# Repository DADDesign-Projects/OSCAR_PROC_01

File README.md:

# OSCAR Processor Board - OSCAR_PROC_01

# 📋 Description
Dedicated electronic board implementing the processor section of the OSCAR effects pedal (https://github.com/DADDesign-Projects/OSCAR_P01A01). This board handles digital signal processing and audio control for the OSCAR effects platform.

# 🛠️ Technical Specifications
## Microcontroller STM32H743:
 - High-performance ARM Cortex-M7 MCU
 -  480 MHz frequency
 -  2MB Flash memory
 -  1MB RAM
## Flash Memory 2* W25Q128
 - 32 Moctet.
 - Double mode 8 bits SPI;
 - 120 Mhz
## SDRAM Memory IS42S16320
 - 64 Moctet
 - 200 Mhz
## USB OTG FS
  - CDC Virtual port COM
  - UDP DownLoad Firmware Update
  - MIDI / USB
## I/O
  - 4 Encoders
  - 2 Switchs
## TFT
  - SPI inteface 
  - 2.4 inch 
## MIDI
  - UART TRS Midi in
## Orogramming/Debugging
  - STLink serial port
  - USB UDP protocol.

## 💻 Software
The circuit design software for this board is available in the OSCAR repository (https://github.com/DADDesign-Projects/OSCAR_P01A01). This project is built upon the DAD Forge framework (https://github.com/DADDesign-Projects/DAD_FORGE), which provides a standardized foundation for hardware development and collaboration.

## 🛠️ Design Tools
This project was entirely designed using KiCad 9.0, the open-source electronics design automation suite.
    
# 📬 Contact
Feel free to contact me for any questions, feedback, improvement suggestions, or collaboration proposals related to the FORGE framework or the OSCAR hardware platform.
I am always open to discussion and community contributions (daddesign.projects@gmail.com).  
  
---

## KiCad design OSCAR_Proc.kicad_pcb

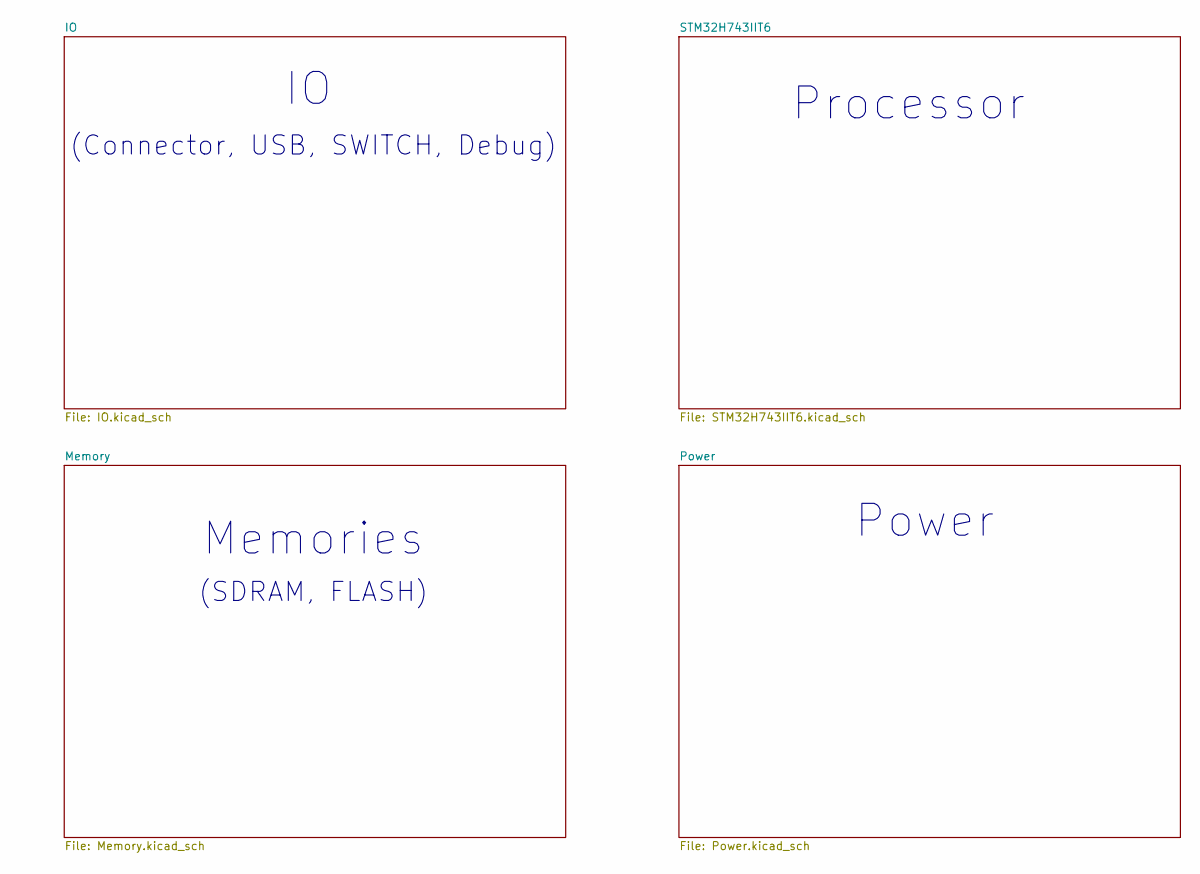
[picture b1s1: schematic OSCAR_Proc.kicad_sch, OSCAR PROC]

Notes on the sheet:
Processor
(Connector, USB, SWITCH, Debug)
Power
(SDRAM, FLASH)
Memories

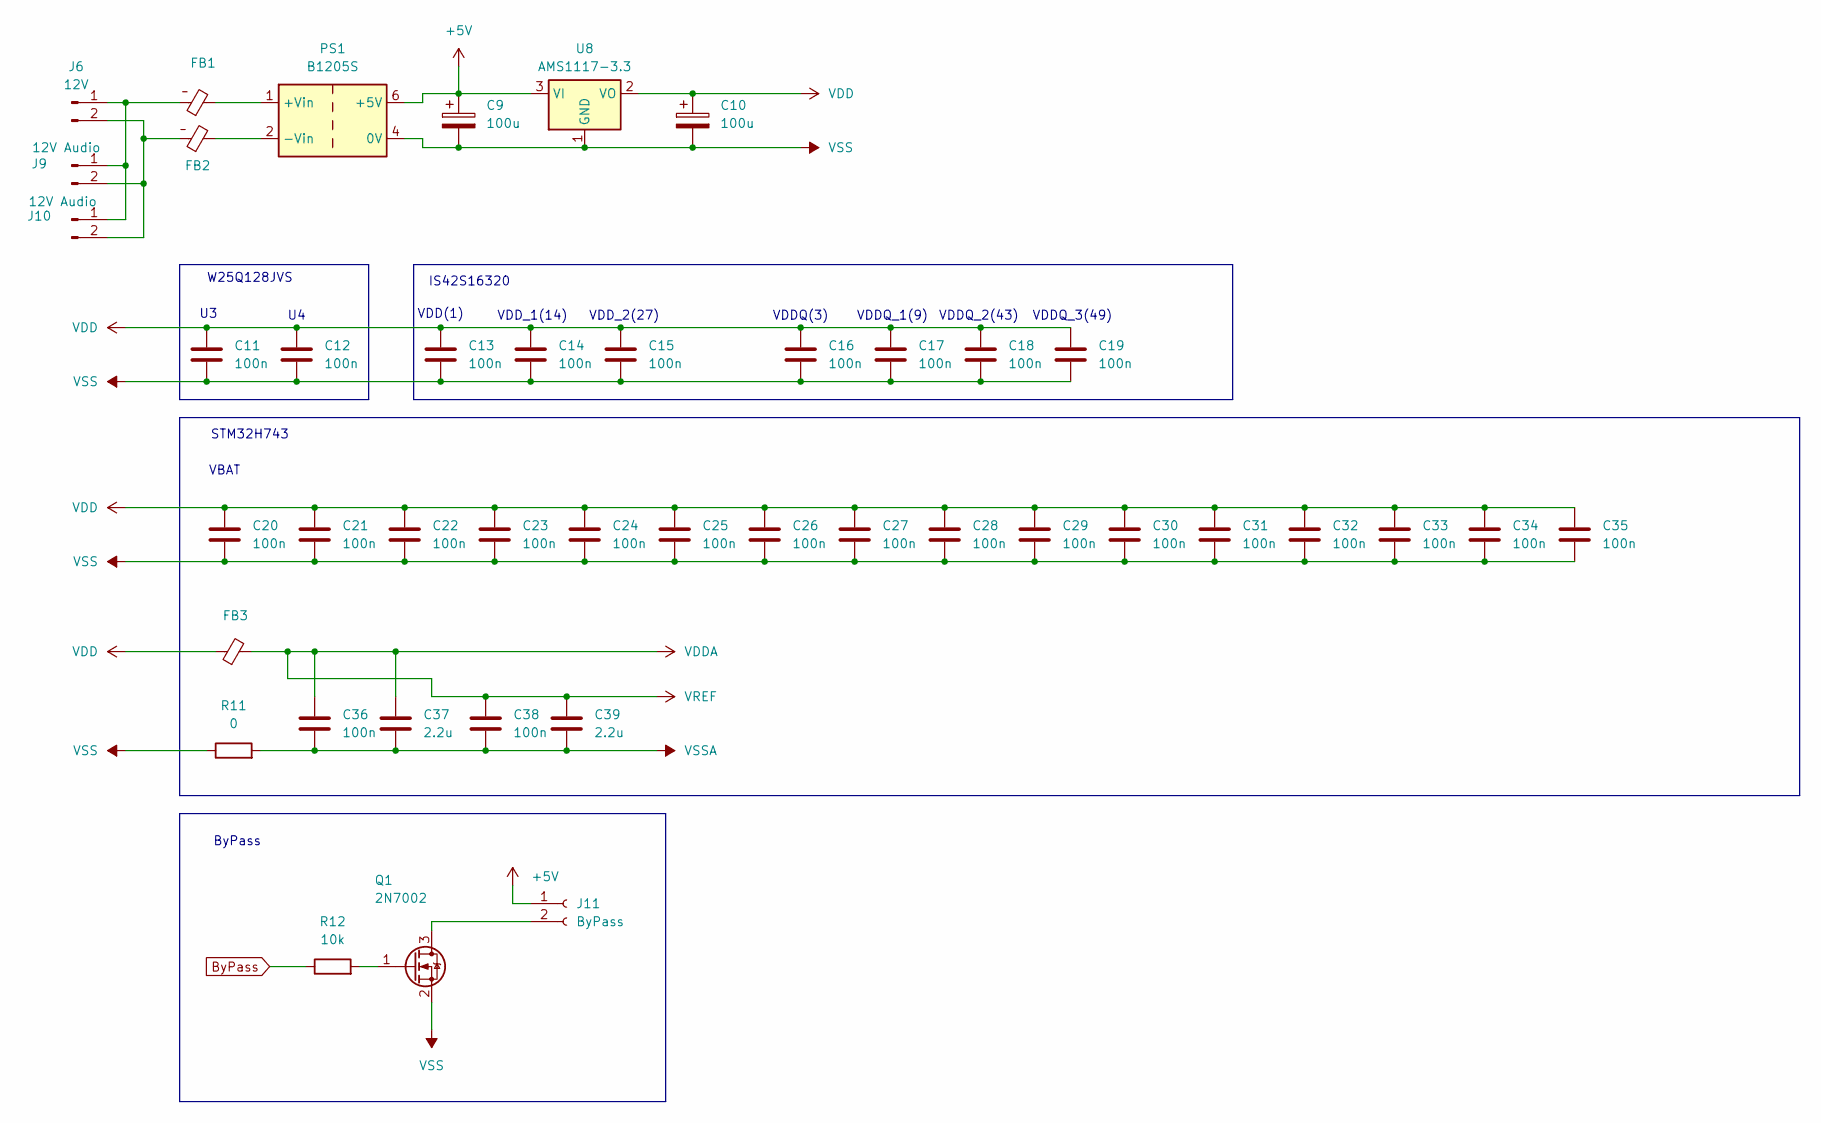
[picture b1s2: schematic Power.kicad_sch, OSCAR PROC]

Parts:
C9, C10: 100u; CP_Elec_6.3x9.9_WM
C11, C12, C13, C14, C15, C16, C17, C18, C19, C20, C21, C22, C23, C24, C25, C26, C27, C28, C29, C30, C31, C32, C33, C34, C35, C36, C38: 100n; C_0805_2012Metric_Pad1.18x1.45mm_HandSolder
C37, C39: 2.2u; C_0805_2012Metric_Pad1.18x1.45mm_HandSolder
FB1, FB2: L_1206_3216Metric_Pad1.22x1.90mm_HandSolder
FB3: L_0805_2012Metric_Pad1.15x1.40mm_HandSolder
J6: 12V; PinHeader_1x02_P2.54mm_Vertical
J9, J10: 12V Audio; PinSocket_1x02_P2.54mm_Vertical
J11: ByPass; PinSocket_1x02_P2.54mm_Vertical
PS1: B1205S; Converter_DCDC_TRACO_TBA1-xxxxE_Single_THT
Q1: 2N7002; SOT-23
R11: 0; R_1206_3216Metric_Pad1.30x1.75mm_HandSolder
R12: 10k; R_1206_3216Metric_Pad1.30x1.75mm_HandSolder
U8: AMS1117-3.3; SOT-223-3_TabPin2

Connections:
+5V: C9.1, J11.1, PS1.6 (+5V), U8.3 (VI)
ByPass: R12.1; also elsewhere on the board
unnamed: FB1.1, J6.1, J9.1, J10.1
unnamed: FB2.1, J6.2, J9.2, J10.2
unnamed: J11.2, Q1.3 (D)
unnamed: FB1.2, PS1.1 (+Vin)
unnamed: FB2.2, PS1.2 (-Vin)
unnamed: Q1.1 (G), R12.2
VDD: C10.1, C11.1, C12.1, C13.1, C14.1, C15.1, C16.1, C17.1, C18.1, C19.1, C20.1, C21.1, C22.1, C23.1, C24.1, C25.1, C26.1, C27.1, C28.1, C29.1, C30.1, C31.1, C32.1, C33.1, C34.1, C35.1, FB3.1, U8.2 (VO); also elsewhere on the board
VDDA: C36.1, C37.1, C38.1, C39.1, FB3.2; also elsewhere on the board
VSS: C9.2, C10.2, C11.2, C12.2, C13.2, C14.2, C15.2, C16.2, C17.2, C18.2, C19.2, C20.2, C21.2, C22.2, C23.2, C24.2, C25.2, C26.2, C27.2, C28.2, C29.2, C30.2, C31.2, C32.2, C33.2, C34.2, C35.2, PS1.4 (0V), Q1.2 (S), R11.1, U8.1 (GND); also elsewhere on the board
VSSA: C36.2, C37.2, C38.2, C39.2, R11.2; also elsewhere on the board

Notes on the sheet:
VDDQ_3(49)
ByPass
STM32H743
VDD(1)
VDD_1(14)
VDD_2(27)
VBAT
IS42S16320
VDDQ(3)
W25Q128JVS
VDDQ_1(9)
VDDQ_2(43)

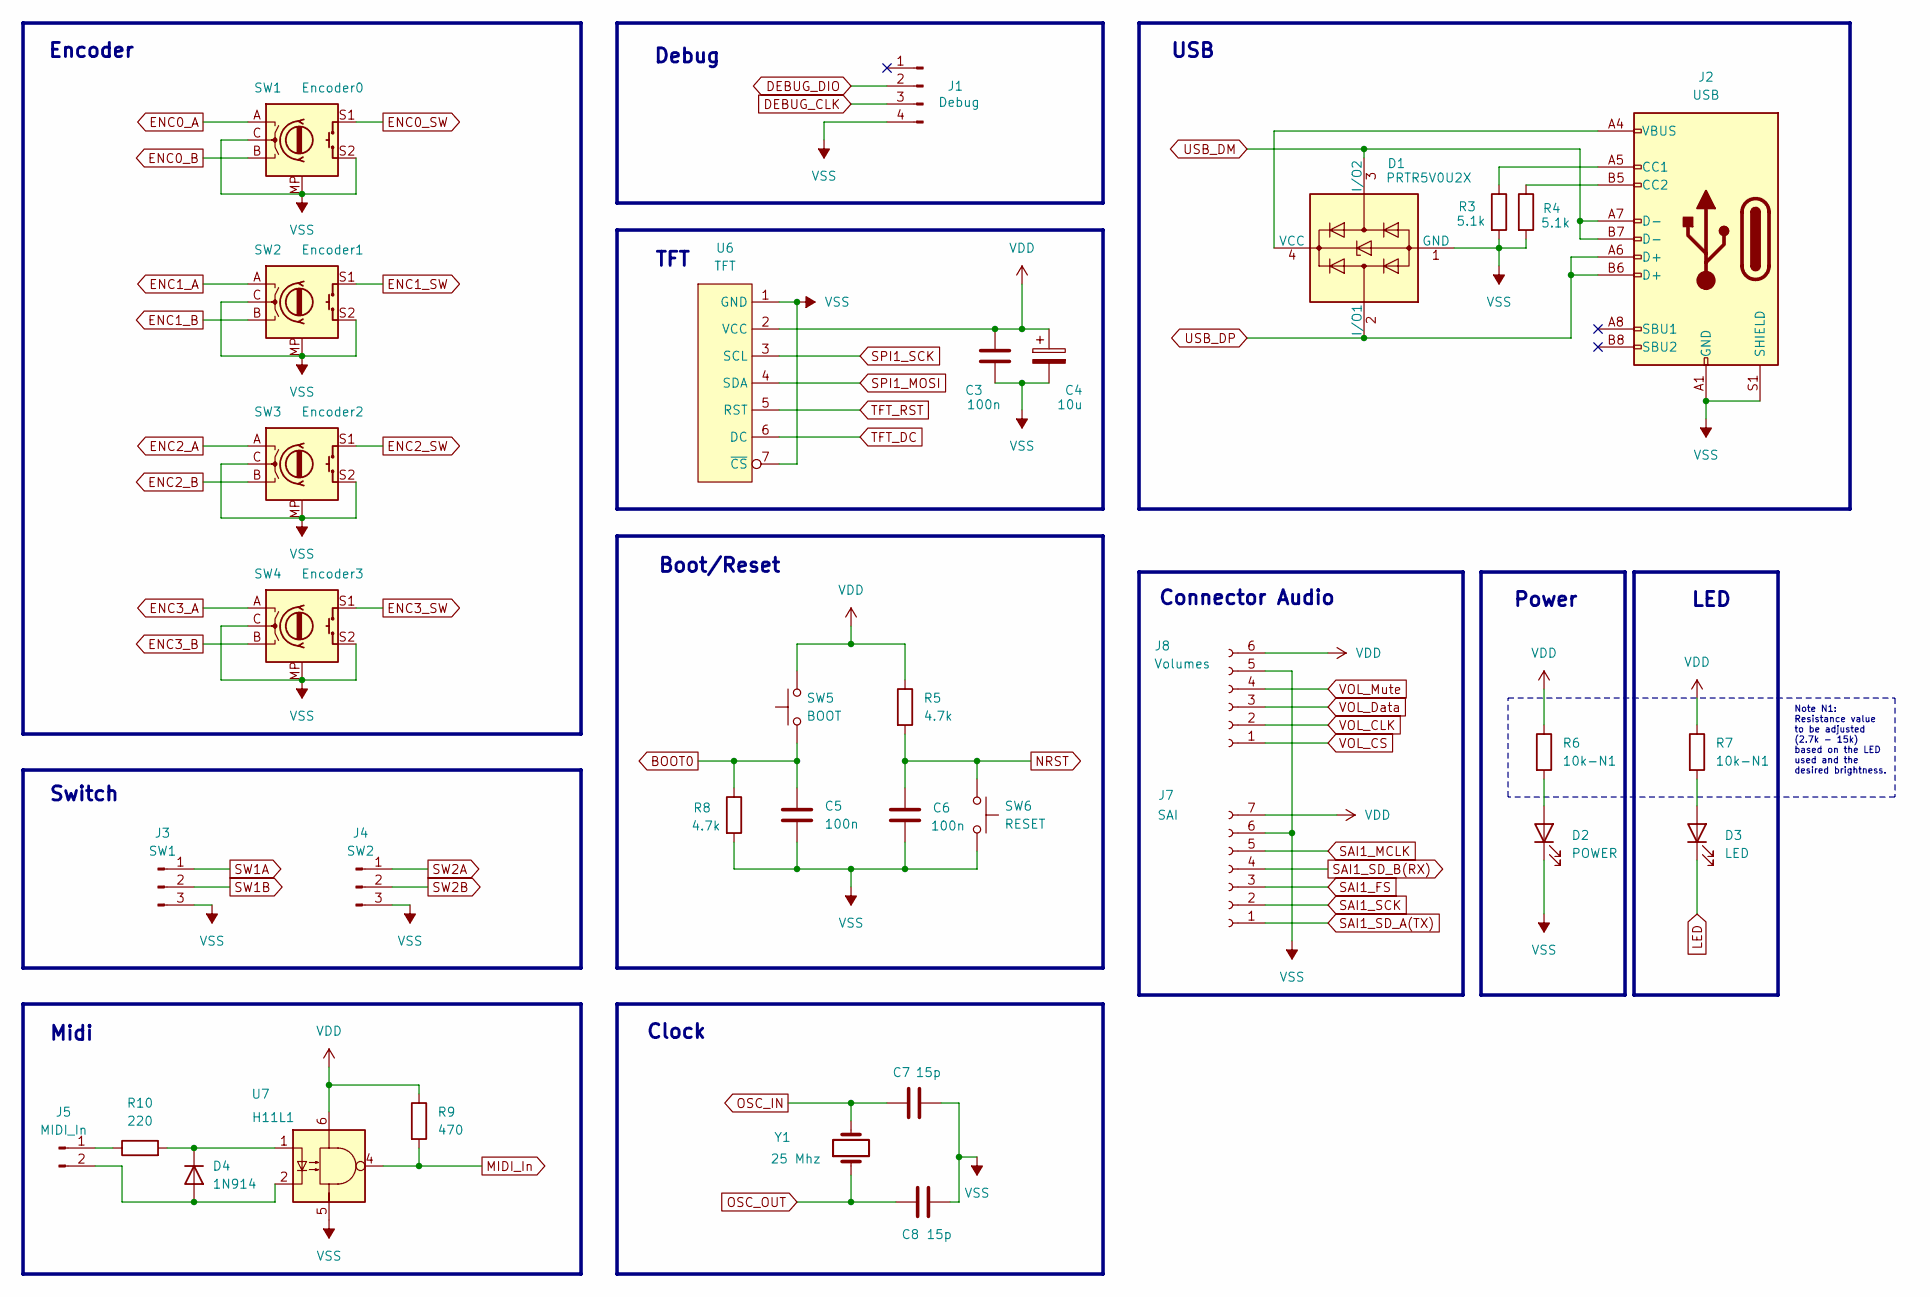
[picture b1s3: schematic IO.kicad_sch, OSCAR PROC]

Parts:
C3, C5, C6: 100n; C_0805_2012Metric_Pad1.18x1.45mm_HandSolder
C4: 10u; CP_EIA-3528-21_Kemet-B_HandSolder
C7, C8: 15p; C_0805_2012Metric_Pad1.18x1.45mm_HandSolder
D1: PRTR5V0U2X; SOT-143
D2: POWER; LED_1206_3216Metric_Pad1.42x1.75mm_HandSolder
D3: LED; LED_1206_3216Metric_Pad1.42x1.75mm_HandSolder
D4: 1N914; D_DO-35_SOD27_P7.62mm_Horizontal
J1: Debug; PinHeader_1x04_P2.54mm_Horizontal
J2: USB; USB_C_Receptacle_HCTL_HC-TYPE-C-16P-01A
J3: SW1; PinSocket_1x03_P2.54mm_Vertical
J4: SW2; PinSocket_1x03_P2.54mm_Vertical
J5: MIDI_In; PinHeader_1x02_P2.54mm_Vertical
J7: SAI; PinSocket_1x07_P2.54mm_Vertical
J8: Volumes; PinSocket_1x06_P2.54mm_Vertical
R3, R4: 5.1k; R_1206_3216Metric_Pad1.30x1.75mm_HandSolder
R5, R8: 4.7k; R_1206_3216Metric_Pad1.30x1.75mm_HandSolder
R6, R7: 10k-N1; R_1206_3216Metric_Pad1.30x1.75mm_HandSolder
R9: 470; R_Axial_DIN0204_L3.6mm_D1.6mm_P7.62mm_Horizontal
R10: 220; R_Axial_DIN0204_L3.6mm_D1.6mm_P7.62mm_Horizontal
SW1: Encoder0; RotaryEncoder
SW2: Encoder1; RotaryEncoder
SW3: Encoder2; RotaryEncoder
SW4: Encoder3; RotaryEncoder
SW5: BOOT; SW_Tactile_SPST_Angled_PTS645Vx39-2LFS
SW6: RESET; SW_Tactile_SPST_Angled_PTS645Vx39-2LFS
U6: TFT; TFT 2.4
U7: H11L1
Y1: 25 Mhz; Quartz

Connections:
BOOT0: C5.1, R8.1, SW5.1; also elsewhere on the board
DEBUG_CLK: J1.3; also elsewhere on the board
DEBUG_DIO: J1.2; also elsewhere on the board
ENC0_A: SW1.A; also elsewhere on the board
ENC0_B: SW1.B; also elsewhere on the board
ENC0_SW: SW1.S1; also elsewhere on the board
ENC1_A: SW2.A; also elsewhere on the board
ENC1_B: SW2.B; also elsewhere on the board
ENC1_SW: SW2.S1; also elsewhere on the board
ENC2_A: SW3.A; also elsewhere on the board
ENC2_B: SW3.B; also elsewhere on the board
ENC2_SW: SW3.S1; also elsewhere on the board
ENC3_A: SW4.A; also elsewhere on the board
ENC3_B: SW4.B; also elsewhere on the board
ENC3_SW: SW4.S1; also elsewhere on the board
LED: D3.1 (K); also elsewhere on the board
MIDI_In: R9.2, U7.4; also elsewhere on the board
NRST: C6.1, R5.2, SW6.1; also elsewhere on the board
unnamed: D1.4 (VCC), J2.A4 (VBUS), J2.A9 (VBUS), J2.B4 (VBUS), J2.B9 (VBUS)
unnamed: D2.2 (A), R6.2
unnamed: D3.2 (A), R7.2
unnamed: D4.2 (A), J5.2, U7.2
unnamed: D4.1 (K), R10.2, U7.1
unnamed: J2.A5 (CC1), R3.1
unnamed: J2.B5 (CC2), R4.1
unnamed: J5.1, R10.1
OSC_IN: C7.1, Y1.2; also elsewhere on the board
OSC_OUT: C8.1, Y1.1; also elsewhere on the board
SAI1_FS: J7.3; also elsewhere on the board
SAI1_MCLK: J7.5; also elsewhere on the board
SAI1_SCK: J7.2; also elsewhere on the board
SAI1_SD_A(TX): J7.1; also elsewhere on the board
SAI1_SD_B(RX): J7.4; also elsewhere on the board
SPI1_MOSI: U6.4 (SDA); also elsewhere on the board
SPI1_SCK: U6.3 (SCL); also elsewhere on the board
SW1A: J3.1; also elsewhere on the board
SW1B: J3.2; also elsewhere on the board
SW2A: J4.1; also elsewhere on the board
SW2B: J4.2; also elsewhere on the board
TFT_DC: U6.6 (DC); also elsewhere on the board
TFT_RST: U6.5 (RST); also elsewhere on the board
USB_DM: D1.3 (I/O2), J2.A7 (D-), J2.B7 (D-); also elsewhere on the board
USB_DP: D1.2 (I/O1), J2.A6 (D+), J2.B6 (D+); also elsewhere on the board
VDD: C3.1, C4.1, J7.7, J8.6, R5.1, R6.1, R7.1, R9.1, SW5.2, U6.2 (VCC), U7.6; also elsewhere on the board
VOL_CLK: J8.2; also elsewhere on the board
VOL_CS: J8.1; also elsewhere on the board
VOL_Data: J8.3; also elsewhere on the board
VOL_Mute: J8.4; also elsewhere on the board
VSS: C3.2, C4.2, C5.2, C6.2, C7.2, C8.2, D1.1 (GND), D2.1 (K), J1.4, J2.A1 (GND), J2.A12 (GND), J2.B1 (GND), J2.B12 (GND), J2.S1 (SHIELD), J3.3, J4.3, J7.6, J8.5, R3.2, R4.2, R8.2, SW1.C, SW1.MP, SW1.S2, SW2.C, SW2.MP, SW2.S2, SW3.C, SW3.MP, SW3.S2, SW4.C, SW4.MP, SW4.S2, SW6.2, U6.1 (GND), U6.7 (~CS), U7.5; also elsewhere on the board

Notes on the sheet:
USB
Clock
TFT
Boot/Reset
Debug
Encoder
Switch
LED
Midi
Power
Connector Audio
Note N1: Resistance value to be adjusted (2.7k - 15k) based on the LED used and the desired brightness.

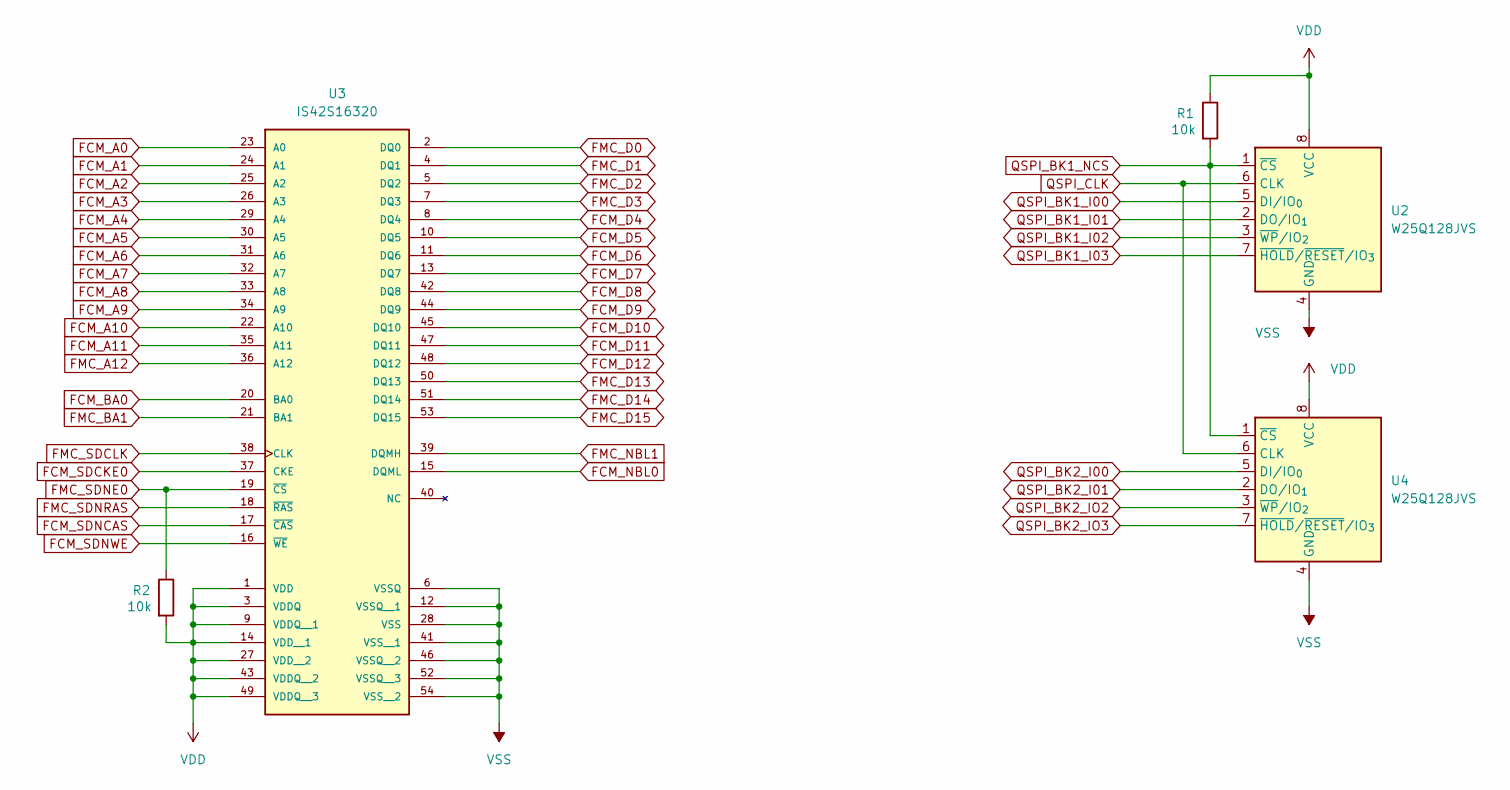
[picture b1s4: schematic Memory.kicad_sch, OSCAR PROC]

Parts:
R1, R2: 10k; R_1206_3216Metric_Pad1.30x1.75mm_HandSolder
U2, U4: W25Q128JVS; SOIC-8_5.3x5.3mm_P1.27mm
U3: IS42S16320; TSOP-II-54_22.2x10.16mm_P0.8mm; PARTREV B1

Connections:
FCM_A0: U3.23 (A0); also elsewhere on the board
FCM_A1: U3.24 (A1); also elsewhere on the board
FCM_A2: U3.25 (A2); also elsewhere on the board
FCM_A3: U3.26 (A3); also elsewhere on the board
FCM_A4: U3.29 (A4); also elsewhere on the board
FCM_A5: U3.30 (A5); also elsewhere on the board
FCM_A6: U3.31 (A6); also elsewhere on the board
FCM_A7: U3.32 (A7); also elsewhere on the board
FCM_A8: U3.33 (A8); also elsewhere on the board
FCM_A9: U3.34 (A9); also elsewhere on the board
FCM_A10: U3.22 (A10); also elsewhere on the board
FCM_A11: U3.35 (A11); also elsewhere on the board
FCM_BA0: U3.20 (BA0); also elsewhere on the board
FCM_D4: U3.8 (DQ4); also elsewhere on the board
FCM_D5: U3.10 (DQ5); also elsewhere on the board
FCM_D6: U3.11 (DQ6); also elsewhere on the board
FCM_D7: U3.13 (DQ7); also elsewhere on the board
FCM_D8: U3.42 (DQ8); also elsewhere on the board
FCM_D9: U3.44 (DQ9); also elsewhere on the board
FCM_D10: U3.45 (DQ10); also elsewhere on the board
FCM_D11: U3.47 (DQ11); also elsewhere on the board
FCM_D12: U3.48 (DQ12); also elsewhere on the board
FCM_NBL0: U3.15 (DQML); also elsewhere on the board
FCM_SDCKE0: U3.37 (CKE); also elsewhere on the board
FCM_SDNCAS: U3.17 (~CAS); also elsewhere on the board
FCM_SDNWE: U3.16 (~WE); also elsewhere on the board
FMC_A12: U3.36 (A12); also elsewhere on the board
FMC_BA1: U3.21 (BA1); also elsewhere on the board
FMC_D0: U3.2 (DQ0); also elsewhere on the board
FMC_D1: U3.4 (DQ1); also elsewhere on the board
FMC_D2: U3.5 (DQ2); also elsewhere on the board
FMC_D3: U3.7 (DQ3); also elsewhere on the board
FMC_D13: U3.50 (DQ13); also elsewhere on the board
FMC_D14: U3.51 (DQ14); also elsewhere on the board
FMC_D15: U3.53 (DQ15); also elsewhere on the board
FMC_NBL1: U3.39 (DQMH); also elsewhere on the board
FMC_SDCLK: U3.38 (CLK); also elsewhere on the board
FMC_SDNE0: R2.1, U3.19 (~CS); also elsewhere on the board
FMC_SDNRAS: U3.18 (~RAS); also elsewhere on the board
QSPI_BK1_NCS: R1.2, U2.1 (~CS), U4.1 (~CS); also elsewhere on the board
QSPI_BK2_I00: U4.5 (DI/IO_{0}); also elsewhere on the board
QSPI_BK2_I01: U4.2 (DO/IO_{1}); also elsewhere on the board
QSPI_BK2_IO2: U4.3 (~WP/IO_{2}); also elsewhere on the board
QSPI_BK2_IO3: U4.7 (~HOLD/~RESET/IO_{3}); also elsewhere on the board
QSPI_CLK: U2.6 (CLK), U4.6 (CLK); also elsewhere on the board
VDD: R1.1, R2.2, U2.8 (VCC), U3.1 (VDD), U3.3 (VDDQ), U3.9 (VDDQ__1), U3.14 (VDD__1), U3.27 (VDD__2), U3.43 (VDDQ__2), U3.49 (VDDQ__3), U4.8 (VCC); also elsewhere on the board
VSS: U2.4 (GND), U3.6 (VSSQ), U3.12 (VSSQ__1), U3.28 (VSS), U3.41 (VSS__1), U3.46 (VSSQ__2), U3.52 (VSSQ__3), U3.54 (VSS__2), U4.4 (GND); also elsewhere on the board

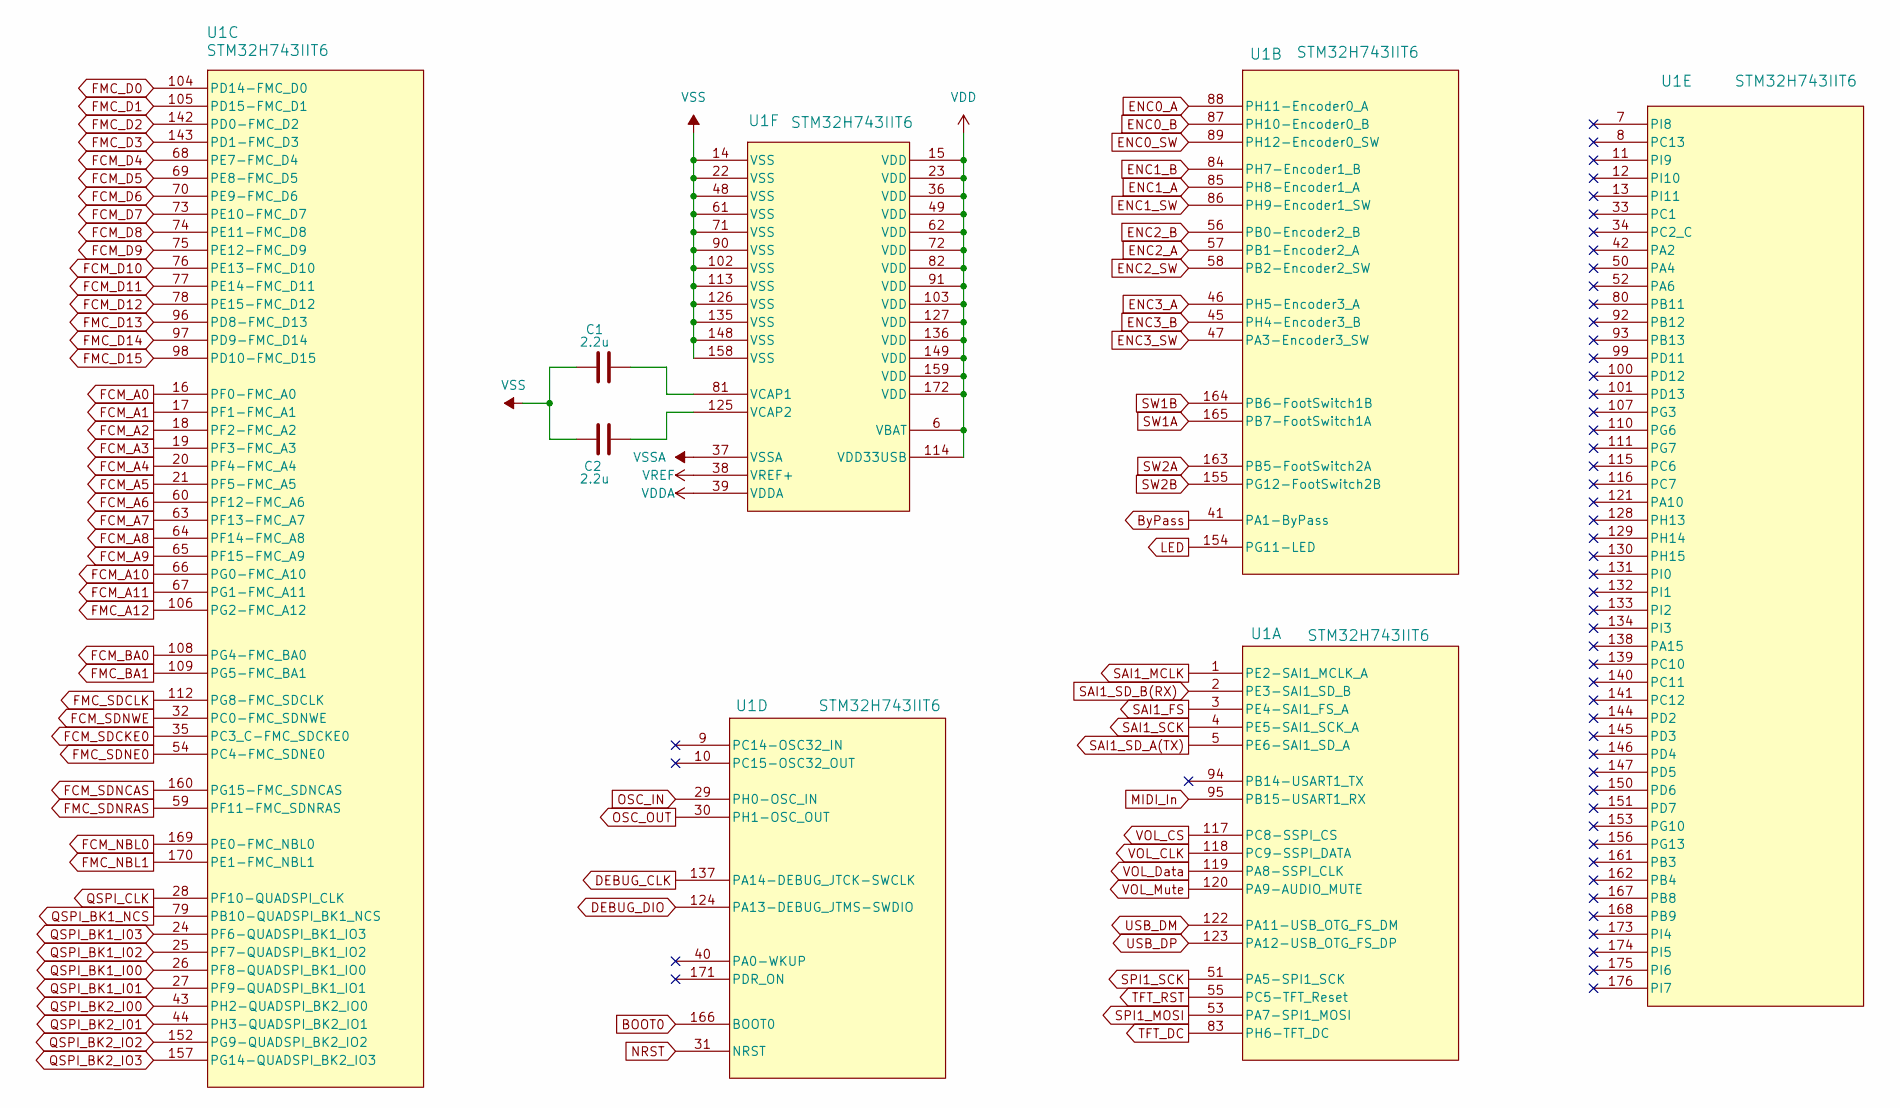
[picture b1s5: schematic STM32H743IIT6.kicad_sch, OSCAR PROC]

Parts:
C1, C2: 2.2u; C_0805_2012Metric_Pad1.18x1.45mm_HandSolder
U1: STM32H743IIT6; LQFP176-24x24mm-M

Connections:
BOOT0: U1.166 (BOOT0); also elsewhere on the board
ByPass: U1.41 (PA1-ByPass); also elsewhere on the board
DEBUG_CLK: U1.137 (PA14-DEBUG_JTCK-SWCLK); also elsewhere on the board
DEBUG_DIO: U1.124 (PA13-DEBUG_JTMS-SWDIO); also elsewhere on the board
ENC0_A: U1.88 (PH11-Encoder0_A); also elsewhere on the board
ENC0_B: U1.87 (PH10-Encoder0_B); also elsewhere on the board
ENC0_SW: U1.89 (PH12-Encoder0_SW); also elsewhere on the board
ENC1_A: U1.85 (PH8-Encoder1_A); also elsewhere on the board
ENC1_B: U1.84 (PH7-Encoder1_B); also elsewhere on the board
ENC1_SW: U1.86 (PH9-Encoder1_SW); also elsewhere on the board
ENC2_A: U1.57 (PB1-Encoder2_A); also elsewhere on the board
ENC2_B: U1.56 (PB0-Encoder2_B); also elsewhere on the board
ENC2_SW: U1.58 (PB2-Encoder2_SW); also elsewhere on the board
ENC3_A: U1.46 (PH5-Encoder3_A); also elsewhere on the board
ENC3_B: U1.45 (PH4-Encoder3_B); also elsewhere on the board
ENC3_SW: U1.47 (PA3-Encoder3_SW); also elsewhere on the board
FCM_A0: U1.16 (PF0-FMC_A0); also elsewhere on the board
FCM_A1: U1.17 (PF1-FMC_A1); also elsewhere on the board
FCM_A2: U1.18 (PF2-FMC_A2); also elsewhere on the board
FCM_A3: U1.19 (PF3-FMC_A3); also elsewhere on the board
FCM_A4: U1.20 (PF4-FMC_A4); also elsewhere on the board
FCM_A5: U1.21 (PF5-FMC_A5); also elsewhere on the board
FCM_A6: U1.60 (PF12-FMC_A6); also elsewhere on the board
FCM_A7: U1.63 (PF13-FMC_A7); also elsewhere on the board
FCM_A8: U1.64 (PF14-FMC_A8); also elsewhere on the board
FCM_A9: U1.65 (PF15-FMC_A9); also elsewhere on the board
FCM_A10: U1.66 (PG0-FMC_A10); also elsewhere on the board
FCM_A11: U1.67 (PG1-FMC_A11); also elsewhere on the board
FCM_BA0: U1.108 (PG4-FMC_BA0); also elsewhere on the board
FCM_D4: U1.68 (PE7-FMC_D4); also elsewhere on the board
FCM_D5: U1.69 (PE8-FMC_D5); also elsewhere on the board
FCM_D6: U1.70 (PE9-FMC_D6); also elsewhere on the board
FCM_D7: U1.73 (PE10-FMC_D7); also elsewhere on the board
FCM_D8: U1.74 (PE11-FMC_D8); also elsewhere on the board
FCM_D9: U1.75 (PE12-FMC_D9); also elsewhere on the board
FCM_D10: U1.76 (PE13-FMC_D10); also elsewhere on the board
FCM_D11: U1.77 (PE14-FMC_D11); also elsewhere on the board
FCM_D12: U1.78 (PE15-FMC_D12); also elsewhere on the board
FCM_NBL0: U1.169 (PE0-FMC_NBL0); also elsewhere on the board
FCM_SDCKE0: U1.35 (PC3_C-FMC_SDCKE0); also elsewhere on the board
FCM_SDNCAS: U1.160 (PG15-FMC_SDNCAS); also elsewhere on the board
FCM_SDNWE: U1.32 (PC0-FMC_SDNWE); also elsewhere on the board
FMC_A12: U1.106 (PG2-FMC_A12); also elsewhere on the board
FMC_BA1: U1.109 (PG5-FMC_BA1); also elsewhere on the board
FMC_D0: U1.104 (PD14-FMC_D0); also elsewhere on the board
FMC_D1: U1.105 (PD15-FMC_D1); also elsewhere on the board
FMC_D2: U1.142 (PD0-FMC_D2); also elsewhere on the board
FMC_D3: U1.143 (PD1-FMC_D3); also elsewhere on the board
FMC_D13: U1.96 (PD8-FMC_D13); also elsewhere on the board
FMC_D14: U1.97 (PD9-FMC_D14); also elsewhere on the board
FMC_D15: U1.98 (PD10-FMC_D15); also elsewhere on the board
FMC_NBL1: U1.170 (PE1-FMC_NBL1); also elsewhere on the board
FMC_SDCLK: U1.112 (PG8-FMC_SDCLK); also elsewhere on the board
FMC_SDNE0: U1.54 (PC4-FMC_SDNE0); also elsewhere on the board
FMC_SDNRAS: U1.59 (PF11-FMC_SDNRAS); also elsewhere on the board
LED: U1.154 (PG11-LED); also elsewhere on the board
MIDI_In: U1.95 (PB15-USART1_RX); also elsewhere on the board
NRST: U1.31 (NRST); also elsewhere on the board
unnamed: C1.2, U1.81 (VCAP1)
unnamed: C2.2, U1.125 (VCAP2)
OSC_IN: U1.29 (PH0-OSC_IN); also elsewhere on the board
OSC_OUT: U1.30 (PH1-OSC_OUT); also elsewhere on the board
QSPI_BK1_I00: U1.26 (PF8-QUADSPI_BK1_IO0); also elsewhere on the board
QSPI_BK1_I01: U1.27 (PF9-QUADSPI_BK1_IO1); also elsewhere on the board
QSPI_BK1_I02: U1.25 (PF7-QUADSPI_BK1_IO2); also elsewhere on the board
QSPI_BK1_I03: U1.24 (PF6-QUADSPI_BK1_IO3); also elsewhere on the board
QSPI_BK1_NCS: U1.79 (PB10-QUADSPI_BK1_NCS); also elsewhere on the board
QSPI_BK2_I00: U1.43 (PH2-QUADSPI_BK2_IO0); also elsewhere on the board
QSPI_BK2_I01: U1.44 (PH3-QUADSPI_BK2_IO1); also elsewhere on the board
QSPI_BK2_IO2: U1.152 (PG9-QUADSPI_BK2_IO2); also elsewhere on the board
QSPI_BK2_IO3: U1.157 (PG14-QUADSPI_BK2_IO3); also elsewhere on the board
QSPI_CLK: U1.28 (PF10-QUADSPI_CLK); also elsewhere on the board
SAI1_FS: U1.3 (PE4-SAI1_FS_A); also elsewhere on the board
SAI1_MCLK: U1.1 (PE2-SAI1_MCLK_A); also elsewhere on the board
SAI1_SCK: U1.4 (PE5-SAI1_SCK_A); also elsewhere on the board
SAI1_SD_A(TX): U1.5 (PE6-SAI1_SD_A); also elsewhere on the board
SAI1_SD_B(RX): U1.2 (PE3-SAI1_SD_B); also elsewhere on the board
SPI1_MOSI: U1.53 (PA7-SPI1_MOSI); also elsewhere on the board
SPI1_SCK: U1.51 (PA5-SPI1_SCK); also elsewhere on the board
SW1A: U1.165 (PB7-FootSwitch1A); also elsewhere on the board
SW1B: U1.164 (PB6-FootSwitch1B); also elsewhere on the board
SW2A: U1.163 (PB5-FootSwitch2A); also elsewhere on the board
SW2B: U1.155 (PG12-FootSwitch2B); also elsewhere on the board
TFT_DC: U1.83 (PH6-TFT_DC); also elsewhere on the board
TFT_RST: U1.55 (PC5-TFT_Reset); also elsewhere on the board
USB_DM: U1.122 (PA11-USB_OTG_FS_DM); also elsewhere on the board
USB_DP: U1.123 (PA12-USB_OTG_FS_DP); also elsewhere on the board
VDD: U1.6 (VBAT), U1.15 (VDD), U1.23 (VDD), U1.36 (VDD), U1.49 (VDD), U1.62 (VDD), U1.72 (VDD), U1.82 (VDD), U1.91 (VDD), U1.103 (VDD), U1.114 (VDD33USB), U1.127 (VDD), U1.136 (VDD), U1.149 (VDD), U1.159 (VDD), U1.172 (VDD); also elsewhere on the board
VDDA: U1.38 (VREF+), U1.39 (VDDA); also elsewhere on the board
VOL_CLK: U1.118 (PC9-SSPI_DATA); also elsewhere on the board
VOL_CS: U1.117 (PC8-SSPI_CS); also elsewhere on the board
VOL_Data: U1.119 (PA8-SSPI_CLK); also elsewhere on the board
VOL_Mute: U1.120 (PA9-AUDIO_MUTE); also elsewhere on the board
VSS: C1.1, C2.1, U1.14 (VSS), U1.22 (VSS), U1.48 (VSS), U1.61 (VSS), U1.71 (VSS), U1.90 (VSS), U1.102 (VSS), U1.113 (VSS), U1.126 (VSS), U1.135 (VSS), U1.148 (VSS), U1.158 (VSS); also elsewhere on the board
VSSA: U1.37 (VSSA); also elsewhere on the board

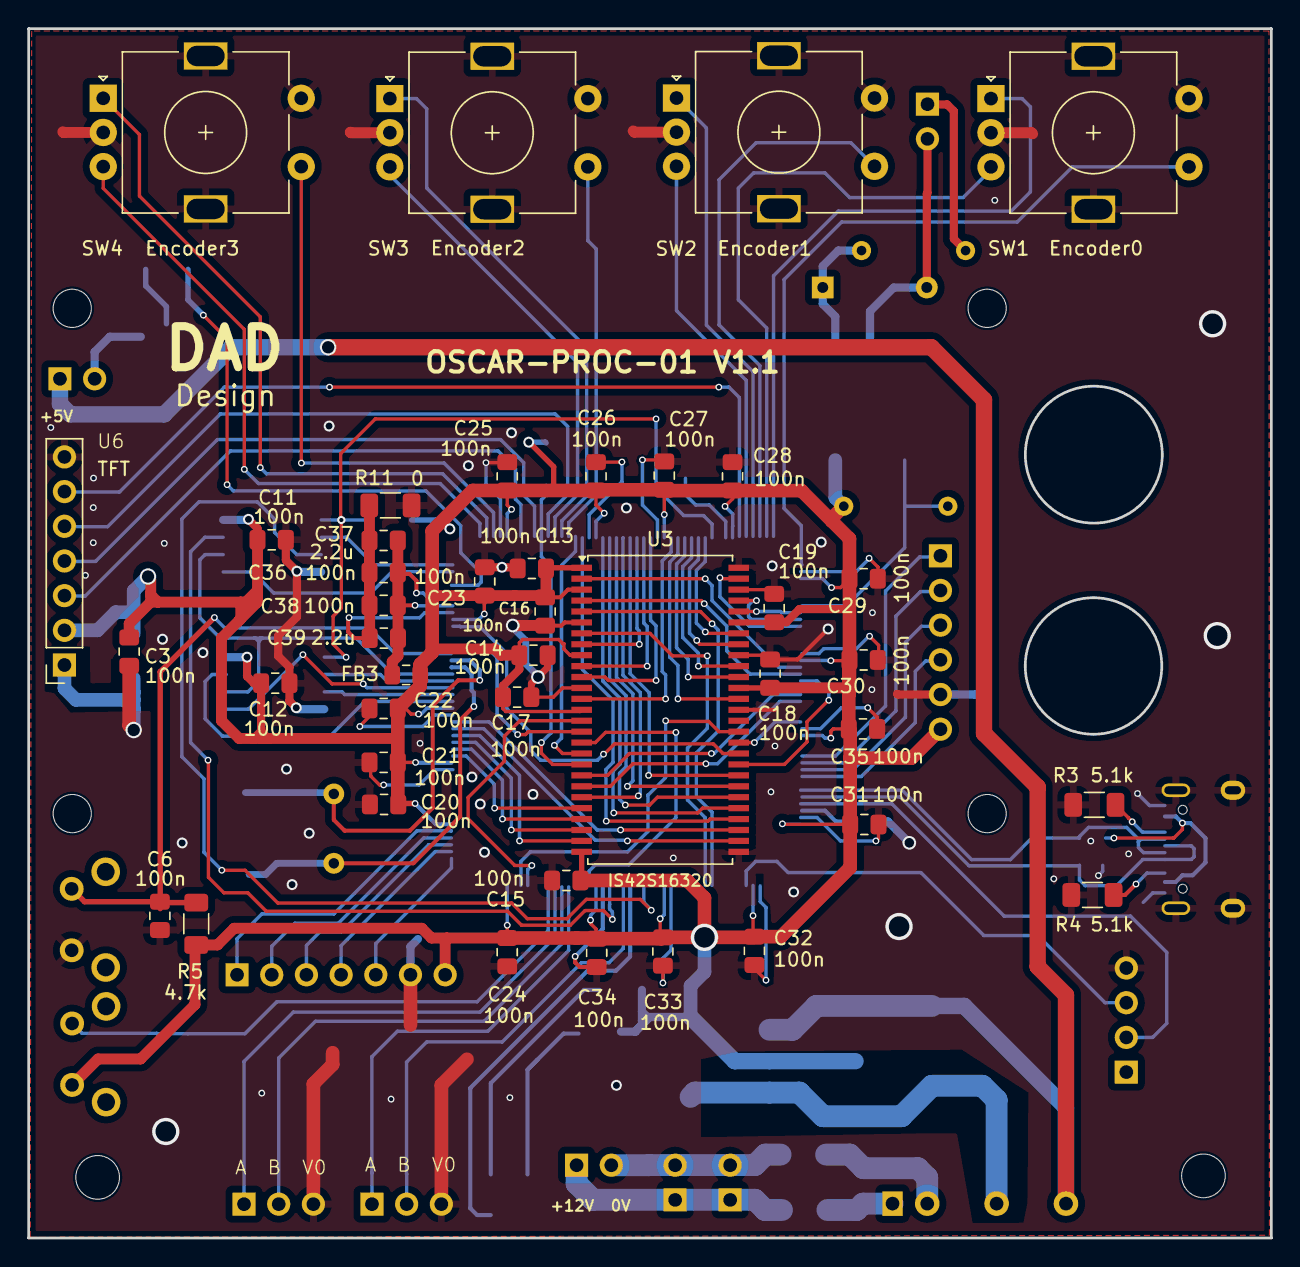
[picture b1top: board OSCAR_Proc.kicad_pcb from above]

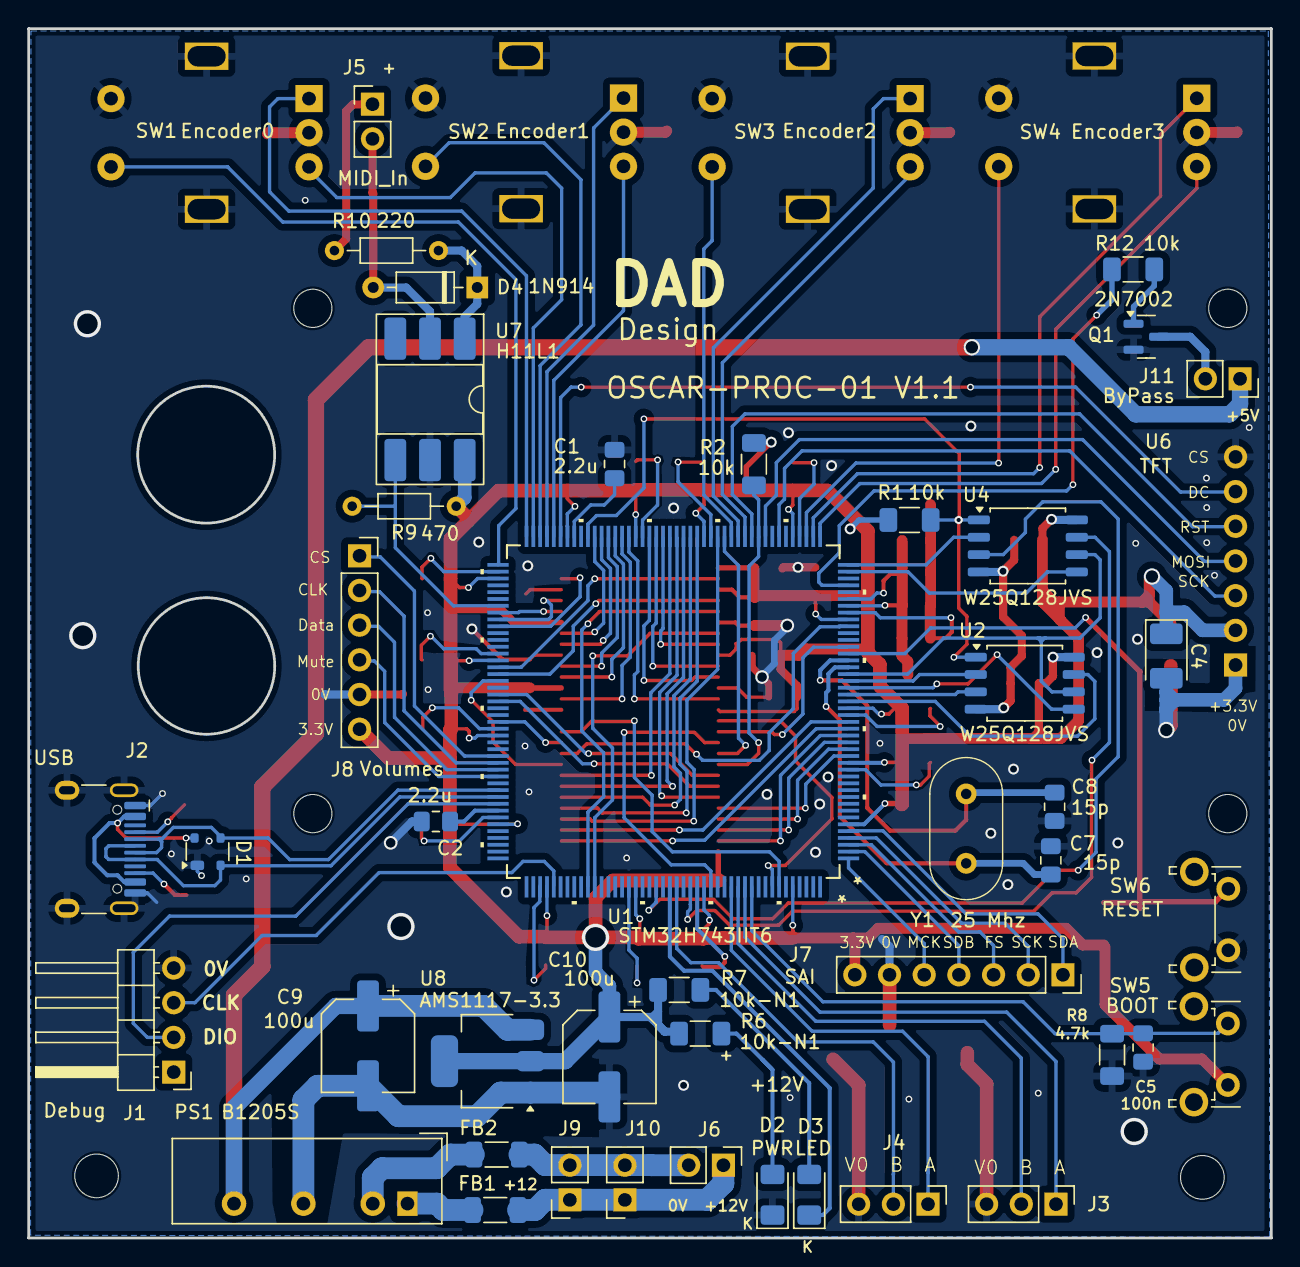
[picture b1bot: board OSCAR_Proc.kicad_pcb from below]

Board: 2 copper layers, 91.0 x 88.6 mm, 87 parts (43 on the bottom side), 110 nets.

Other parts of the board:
H1: MountingHole_3.2mm_M3
U2#2: W25Q128JVS; SOIC-8_5.3x5.3mm_P1.27mm

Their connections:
QSPI_BK1_I00: U2#2.5 (DI/IO_{0}); also elsewhere on the board
QSPI_BK1_I01: U2#2.2 (DO/IO_{1}); also elsewhere on the board
QSPI_BK1_I02: U2#2.3 (~WP/IO_{2}); also elsewhere on the board
QSPI_BK1_I03: U2#2.7 (~HOLD/~RESET/IO_{3}); also elsewhere on the board
QSPI_BK1_NCS: U2#2.1 (~CS); also elsewhere on the board
QSPI_CLK: U2#2.6 (CLK); also elsewhere on the board
VDD: U2#2.8 (VCC); also elsewhere on the board
VSS: U2#2.4 (GND); also elsewhere on the board

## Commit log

2025-11-16 Enhance README with project details and specifications
    Updated README to include detailed project description, technical specifications, and contact information.
2026-02-25 Reposition footswitch connectors and LEDs
    - Moved footswitch connectors to support vertical placement
    - Adjusted LED positions for better visibility
2026-04-04 Reposition footswitch connectors and LEDs

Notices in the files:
README.md:
License: MIT
